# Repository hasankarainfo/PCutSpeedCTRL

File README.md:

# PCutSpeedCTRL Constant Speed Controller

<ul align="left">
    <li>It provides constant speed operation and remote control of single phase AC motor suitable for operation with 220 vac 50hz.</li>
    <li>When produced with BTA41 triac switching element, it provides usage up to 40 Ampere. In my initial tests I used a 1.2kW AC motor.</li>
    <li>The first version component cost was calculated as $3,075.</li>
    <li>Suitable for use with standard hand milling motors that are easily available on the world market.</li>
    <li>The mentioned milling motors are suitable for use in CNC machines.</li>
    <li>Any CNC controller can be connected directly and in isolation with a standard PWM output.</li>
    <li>This resource contains design and production files for hardware and firmware.</li>
    <li>PC Software used in the development process; KICAD 9 for Hardware, MOUNRIVER 2.1 IDE and C programming language were used for Firmware. OCTAVE was used to create look up tables for some mathematical equations.</li>
    <li> <a href="https://youtu.be/PU_BxYYPQiw ">Test Video Youtube Link</a>  </li>  
</ul>  

<table align="center" width=90%>
<tr>       
<td align="center"></td>
<td align="center"></td>  
</tr>

<tr>  
<td align="center"> <b>3D Front</b></td>
<td align="center"> <b>3D Rear</b></td>
</tr>
</table>

## HARDWARE Detail:

### Schematic Detail:
<table align="center" width=90%>
    <tr>       
        <td style="width:70%"></td>
        <td>
        Non Isolated Power Supply:
            <ul><i> 
                <li> A cost-effective, non-isolated design was implemented for low voltage supply needs.  </li> 
                <li> This scheme can meet the required 30mA power requirement. This power is mainly used for MCU operation, hall effect sensor operation and TRIAC triggering.</li> 
            </i></ul>
        </td>  
    </tr>
</table>

<table align="center" width=90%>
    <tr>       
        <td style="width:70%"></td>
        <td> 
        Triac gate drive circuit:
            <ul><i>
            <li>Phase cut topology used.</li> 
            <li> Some snubber components applied.</li> 
            </i></ul>
        </td>  
    </tr>
</table>
<table align="center" width=90%>
    <tr>       
        <td style="width:70%"></td>
        <td> 
        Zero cross detection circuit:
            <ul><i>
            <li>With q3 mosfet, a faster falling edge signal is generated.
            </li> 
            </i></ul>
        </td>  
    </tr>
</table>

<table align="center" width=90%>
    <tr>       
        <td style="width:70%"></td>
        <td> 
        MCU, Hall Sensor and PWM Input Circuit:
            <ul><i>
            <li>It was developed using the ch32v003j4m6 microcontroller from wch company.</li>
            <li> DRV5023 hall sensor was used for spindle speed measurement.</li> 
            </i></ul>
        </td>  
    </tr>
</table>

### Panelize Detail:
<ul align="left">
    <li>We use the Kikit plugin for PCB paneling.</li>
    <li>We can panelize the PCB design by running the panelize_multiple.py file located in the "/HW/Panelize/" file path.</li>
    <li>Phase cut topology used.</li>
    <li>In panelized form, a new kicad project is created automatically.</li>
</ul>  

<table align="center" width=90%>
<tr>       
<td  style="width:65%"></td>
<td></td>  
</tr>

<tr>  
<td align="center"> <b> Panelize Wiew </b> </td>
<td align="center"> <b> Some Panel Settings in panelize_multiple.py </b></td>
</tr>
</table>

## Mechanic Detail:
<ul align="left"> 
    <li> When the AC motor top cover is opened, 4 screw holes can be seen. 
    </li>
    <li> When the top cover of the spindle motor is first opened, there will be no hole in the middle 
    </li>
    <li> A metric 5 diameter hole should be drilled along the shaft, coinciding with the center.
    </li>
    <li> While designing the PCB, compatibility was ensured by using the Mac Allister manufacturer MSR1200 model AC motor. 
    </li>
</ul>

<table align="center" width=90% >
    <tr>       
        <td style="width:70%"></td>
        <td> 
            <ul>
                <li>
                    A 3x3 mm cylindrical neodymium magnet is inserted through this hole and coupled with the shaft.
                </li>
                <li>There should be an angle of approximately ~45° between the magnet cylinder center axis and the shaft axis. 
                </li>
                <li>The shaft and magnet can be attached using super glue.
                </li>
            </ul>
        </td>  
    </tr>
</table>

<p align="center"> <b> When the rotor is turned to different angles, it should be confirmed that the magnet rotates together. </b> </p>

<table align="center" width=90% >
    <tr>
        <td>  
            
            <p align="center"> <b> Spindle Motor Controller assembly demonstration </b> </p>
        </td>
        <td> 
            
            <p align="center"> <b> Spindle Motor Controller Driver Applied </b> </p>
        </td>
    </tr>
</table>

## Firmware Detail:

<ul align="left">
    <li>MOUNRIVER 2.1 IDE and C programming language were used for Firmware.</li>
    <li>The HYB cooperative operating system was used for the MCU resource management organization. </li>
    <li>Since the cooperative real-time operating system we use is very lightweight, it can easily adapt to the Microcontroller despite its weak memory.
    </li>
    <li> With this project, I am also sharing the cooperative operating system that I have been developing over the years as open source.</li>
    <li> I also added some libraries to the firmware that are not actively in use but could enable developments that fit the structure of the project.
    </li>
    <li>NTC temperature sensor data interpretation, ADC reading, moving average filter, some of them. 
    </li>
</ul>  

### About the main routine:
<ul align="left">
    <li>Using 2 different input capture modules, PWM input data was taken with IC1 and the magnetic sensor digital output frequency value was measured with IC2.</li>
    <li>Speed ​​change commands have been smoothed to create a ramp between the PWM data and the target speed information.</li>
    <li>Zero Cross detection was performed using the external interrupt module. Triac triggering and PID routines were run with each ZC detection.</li>
    <li>For linearization of the system, the source signal is assumed to be a sinusoidal signal. The equation used is the integral of the half sine signal.</li>
    <li>For system linearization, PID output information was applied to the linearization function using the look up table interpolation created with the Octave PC application.</li>
    <li>Thus, a more stable closed-loop system was obtained with fixed PID coefficients.
    </li>
    <li>Duty data was evaluated as time data to convert it into TRIAC switch signal.</li>
    <li>In addition to the look up table, a firmware setting option has been added to enable linearization by measurement method.
    </li>
    <li>The firmware can be made to work with different features with a set of predefined settings.</li>
    <li>The mentioned settings can be seen in the image below, as well as in the main.c file.</li>
</ul>  

<td >  
    
    <p align="center"> <b> Firmware Managment Settings 1 </b> </p>
</td>

<td> 
    
    <p align="center"> <b> Firmware Managment Settings 2 </b> </p>
</td>

### Octave Equations Plot and Print :
<ul align="left">
    <li>The linearization table created with Octave PC software can be examined graphically and can be evaluated by copying and pasting directly into the C code.</li>
    <li>Similarly, the linearization table output from the MCU serial port output at boot up time can be directly copied and pasted into the Octave software and visually inspected. </li>
</ul>  

<table align="center" width=90% >
    <tr>
        <td>  
            
            <p align="center"> <b> Inverse Sine Power Equation Created</b> </p>
        </td>
        <td> 
            
            <p align="center"> <b> Inverse Sine Power from MCU, Equation and Measured </b> </p>
        </td>
    </tr>
</table>

## Some Tests:

<ul align="left">
    <li>As can be watched in the video link shared above, we performed some aluminum sheet and PCB drilling tests.</li>
    <li>When we apply sudden strain and sudden release tests, overshooting values ​​of up to 800 rpm occur.</li>
    <li>The spindle motor we tested has a 30k rpm feature at full power.</li>
    <li>As is known, keeping a constant speed at low rotational speeds can be a very challenging goal.</li>
    <li>Its ability to remain at low overshoot values ​​while at 1k rmp target speed is at a satisfactory level.
    </li>
    <li>We could observe that it does not work so stably unless linearization is applied.</li>
    <li>We made it possible to observe the result by disabling a single predefined setting via the firmware.</li>
</ul>  

<td >  
    
    <p align="center"> <b> PCB Milling and Edge Cut Test Front </b> </p>
</td>

<td> 
    
    <p align="center"> <b> PCB Milling and Edge Cut Test Rear </b> </p>
</td>

## Production:
<ul align="left">
    <li> Gcode files created for PCB production with DIY techniques can be found in the HW/Panelize/Plot_diy folder.
    </li>
    <li>The bom list, along with supply links and unit prices, can be viewed in the "HW/bom" file path.</li>
    <li>For PCB fabrication files, files in the "HW/Plot" or "HW/Panelize/Plot" file path can be compressed and shared directly with the PCB manufacturer.</li>
</ul>

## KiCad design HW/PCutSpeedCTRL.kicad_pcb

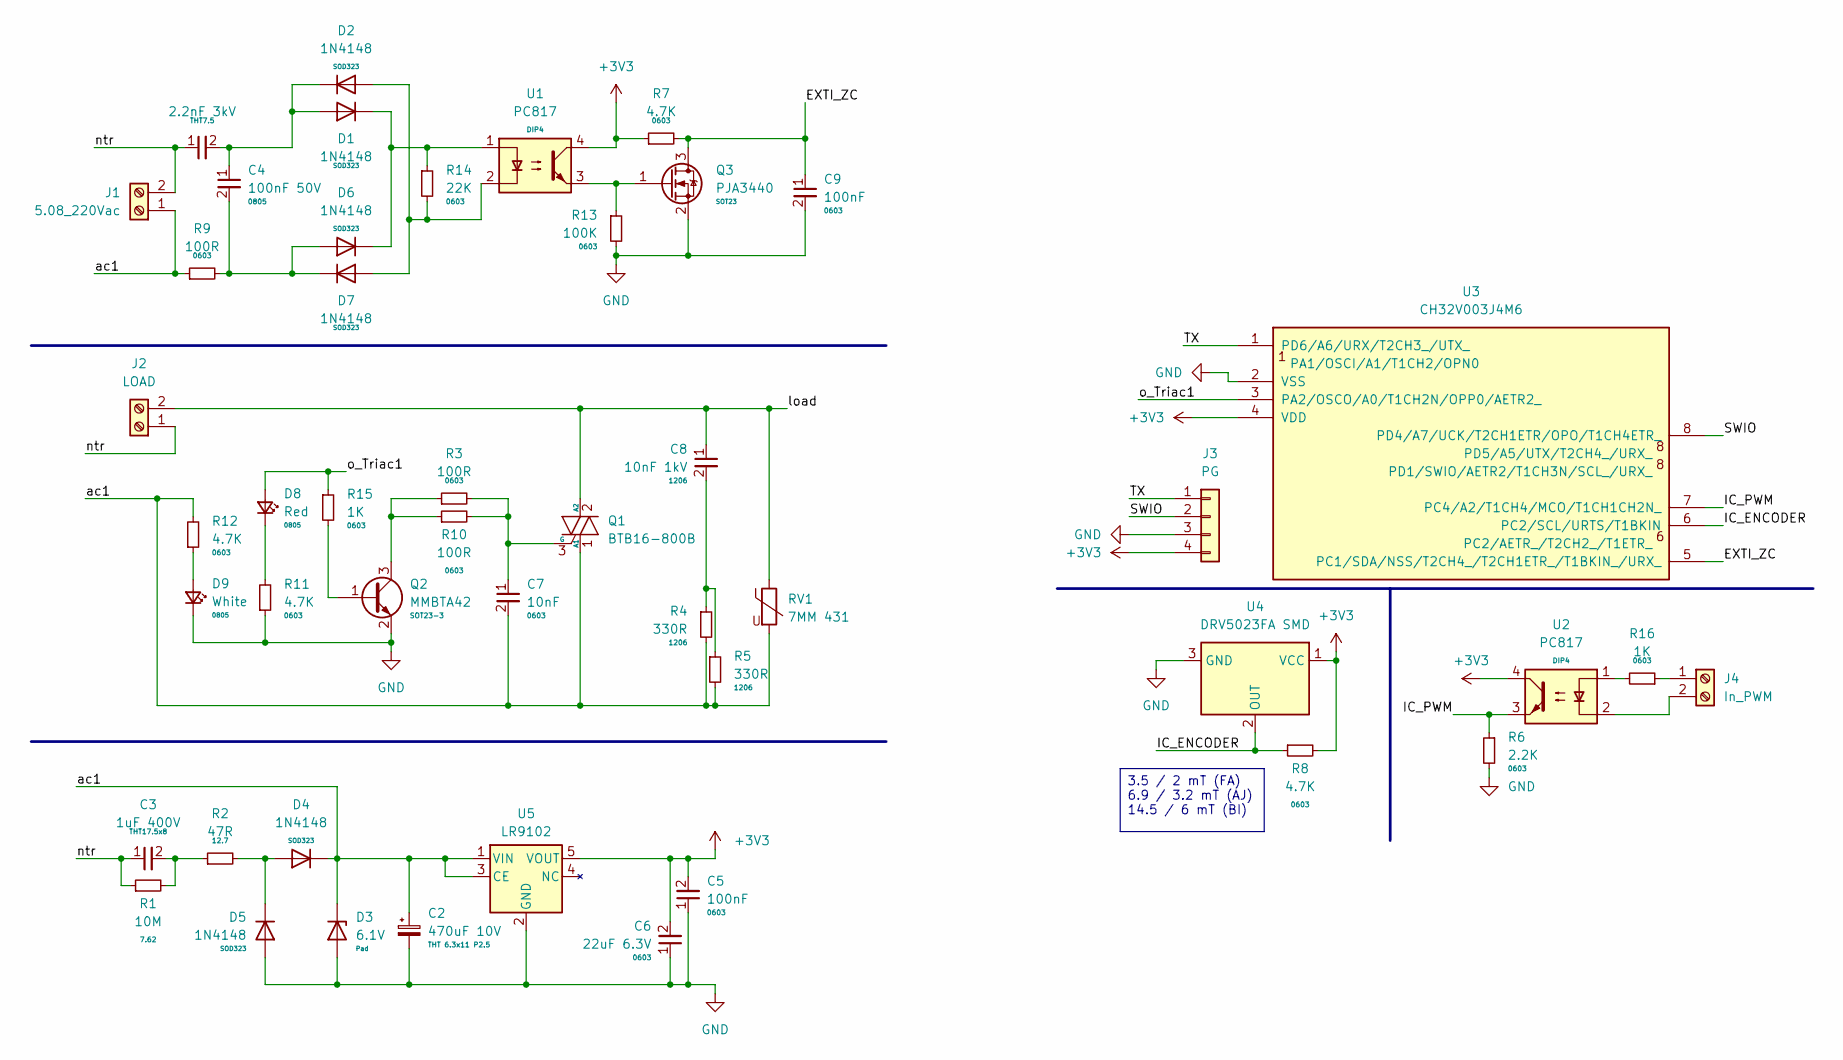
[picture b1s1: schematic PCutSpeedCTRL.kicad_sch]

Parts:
C1: 2.2nF 3kV; C_Disc_D7.5mm_W5.0mm_P7.50mm; Part Number CK45-B3FD222KYNNA
C2: 470uF 10V; CP_Radial_D6.3mm_H11.0mm_P2.50mm; Part Number PKLH-010V471ME110-T2.5
C3: 1uF 400V; C_Rect_L18.0mm_W8.0mm_P15.00mm_FKS3_FKP3; Part Number KOM.KND.03.000133
C4: 100nF 50V; C_0805_2012Metric_SmallPad; Part Number CC0805KRX7R9BB104
C5, C9: 100nF; C_0603_1608Metric_SlimPad; Part Number CC0603KRX7R9BB104
C6: 22uF 6.3V; C_0603_1608Metric; Part Number CL10A226MQ8NRNC
C7: 10nF; C_0603_1608Metric_SlimPad; Part Number CL10B103KB8NNNC
C8: 10nF 1kV; C_1206_3216Metric_SlimPad; Part Number CC1206KKX7RCBB103
D1, D2, D4, D5, D6, D7: 1N4148; D_SOD-123F-s; Part Number 1N4148WS-HT
D3: 6.1V; D_SOD-123F-s; Part Number ZMD6.2
D8: Red; LED_0805_2012Metric-s; Part Number HL-PSC-2012H233W-HF4
D9: White; LED_0805_2012Metric-s; Part Number HL-PSC-2012H233W-HF4
J1: 5.08_220Vac; TerminalBlock_MetzConnect_Type101_RT01602HBWC_1x02_P5.08mm_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; Part Number ZB2EDGV-5.08-2P
J2: LOAD; TerminalBlock_MetzConnect_Type101_RT01602HBWC_1x02_P5.08mm_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; Part Number ZB2EDGV-5.08-2P
J3: PG; PinHeader_1x04_P2.54mm_Vertical
J4: In_PWM; TerminalBlock_4Ucon_1x02_P3.50mm_Horizontal; Part Number 15EDGVC-3.5-02P-12-00AH
Q1: BTB16-800B; TO-220-3_Vertical_HV_TO247_Applied
Q2: MMBTA42; SOT-23-3-s; Part Number MMBTA42_R1_00001
Q3: PJA3440; SOT-23-3-s; Part Number PJA3440_R2_00001
R1: 10M; R_Axial_DIN0207_L6.3mm_D2.5mm_P15.24mm_Horizontal; Part Link Part Link
R2: 47R; R_Axial_DIN0309_L9.0mm_D3.2mm_P2.54mm_Vertical; Part Link Part Link
R3, R9, R10: 100R; R_0603_1608Metric; Part Number 0603SAF1000T5E
R4, R5: 330R; R_1206_3216Metric_SlimPad; Part Number 1206S4F3300T5E
R6: 2.2K; R_0603_1608Metric; Part Number RC0603FR-072K2L
R7, R8, R11, R12: 4.7K; R_0603_1608Metric; Part Number RC0603FR-074K7L
R13: 100K; R_0603_1608Metric; Part Number 0603SAF1003T5E
R14: 22K; R_0603_1608Metric; Part Number 0603SAF2202T5E
R15, R16: 1K; R_0603_1608Metric; Part Number 0603SAF1001T5E
RV1: 7MM 431; RV_Disc_D15.5mm_W5.4mm_P7.5mm_Spec; Part Number TVR07431KSABY
U1, U2: PC817; DIP-4_W7.62mm; Part Number UPC817CG-D04-T
U3: CH32V003J4M6; SO-8_3.9x4.9mm_P1.27mm; Part Number CH32V003J4M6
U4: DRV5023FA SMD; SOT-23-3-s; Part Number 296-49623-1-ND
U5: LR9102; TSOT-23-5_SlimPad; Part Number LR9102G-33-AF5-R

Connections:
+3V3: C5.2, C6.2, J3.4, R7.1, R8.2, U1.4, U2.4, U3.4 (VDD), U4.1 (VCC), U5.5 (VOUT)
/EXTI_ZC: C9.1, Q3.3 (D), R7.2, U3.5 (PC1/SDA/NSS/T2CH4_/T2CH1ETR_/T1BKIN_/UR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)
/IC_ENCODER: R8.1, U3.6 (PC2/SCL/URTS/T1BKIN), U4.2 (OUT)
/IC_PWM: R6.1, U2.3, U3.7 (PC4/A2/T1CH4/MCO/T1CH1CH2N_)
/SWIO: J3.2, U3.8 (PD4/A7/UCK/T2CH1ETR/OPO/T1CH4ETR_)
/TX: J3.1, U3.1 (PD6/A6/URX/T2CH3_/UTX_)
/ac1: C2.1, C7.2, D3.1 (K), D4.1 (K), J1.1, Q1.1 (A1), R4.2, R5.2, R9.1, R12.2, RV1.2, U5.1 (VIN), U5.3 (CE)
/load: C8.1, J2.2, Q1.2 (A2), RV1.1
/ntr: C1.1, C3.1, J1.2, J2.1, R1.1
/o_Triac1: D8.2 (A), R15.1, U3.3 (PA2/OSCO/A0/T1CH2N/OPP0/AETR2_)
GND: C2.2, C5.1, C6.1, C9.2, D3.2 (A), D5.2 (A), D9.1 (K), J3.3, Q2.2 (E), Q3.2 (S), R6.2, R11.1, R13.2, U3.2 (VSS), U4.3 (GND), U5.2 (GND)
unnamed: C3.2, R1.2, R2.1
unnamed: C8.2, R4.1, R5.1
unnamed: C1.2, C4.1, D1.2 (A), D2.1 (K)
unnamed: D1.1 (K), D6.1 (K), R14.1, U1.1
unnamed: D2.2 (A), D7.2 (A), R14.2, U1.2
unnamed: D4.2 (A), D5.1 (K), R2.2
unnamed: C4.2, D6.2 (A), D7.1 (K), R9.2
unnamed: D8.1 (K), R11.2
unnamed: D9.2 (A), R12.1
unnamed: J4.1, R16.1
unnamed: J4.2, U2.2
unnamed: C7.1, Q1.3 (G), R3.2, R10.2
unnamed: Q2.1 (B), R15.2
unnamed: Q2.3 (C), R3.1, R10.1
unnamed: Q3.1 (G), R13.1, U1.3
unnamed: R16.2, U2.1

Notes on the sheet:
3.5 / 2 mT (FA) 6.9 / 3.2 mT (AJ) 14.5 / 6 mT (BI)

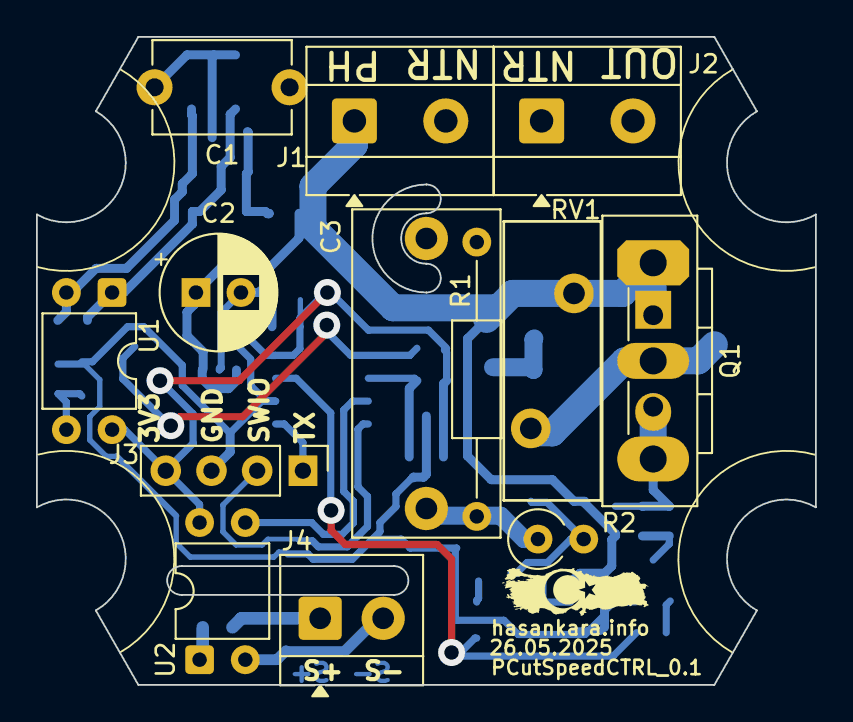
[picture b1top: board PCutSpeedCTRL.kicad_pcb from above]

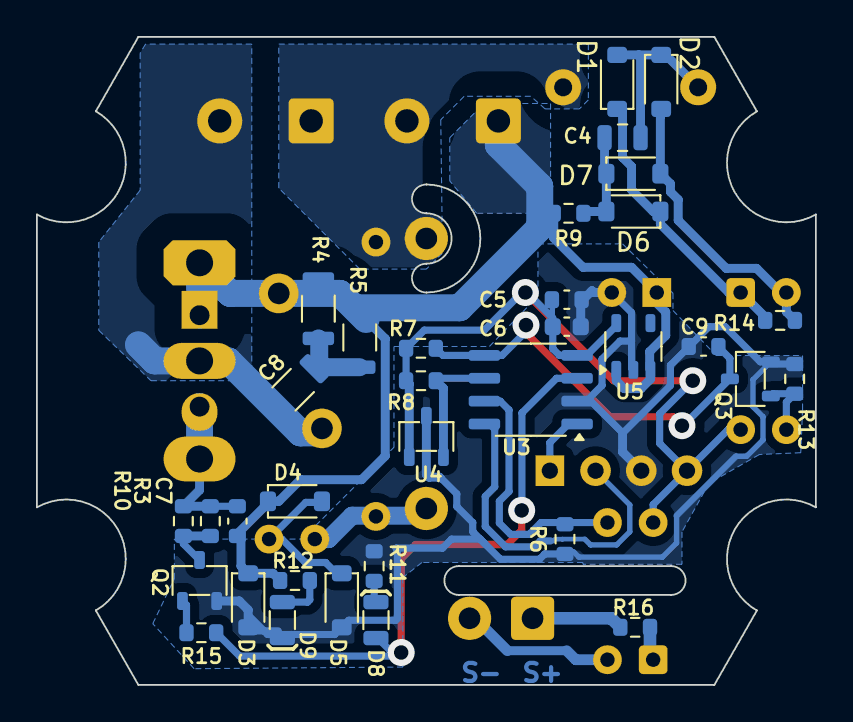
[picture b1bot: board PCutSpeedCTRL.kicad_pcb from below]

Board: 2 copper layers, 43.3 x 36.0 mm, 47 parts (34 on the bottom side), 27 nets.

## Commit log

2025-05-27 LICENSE file added
